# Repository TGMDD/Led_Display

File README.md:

This repository contains schematic and PCB design for a 24X8 Led Display using shift registers 74HC595. 
Note: The PCB is designed for the 5mm flat leds.

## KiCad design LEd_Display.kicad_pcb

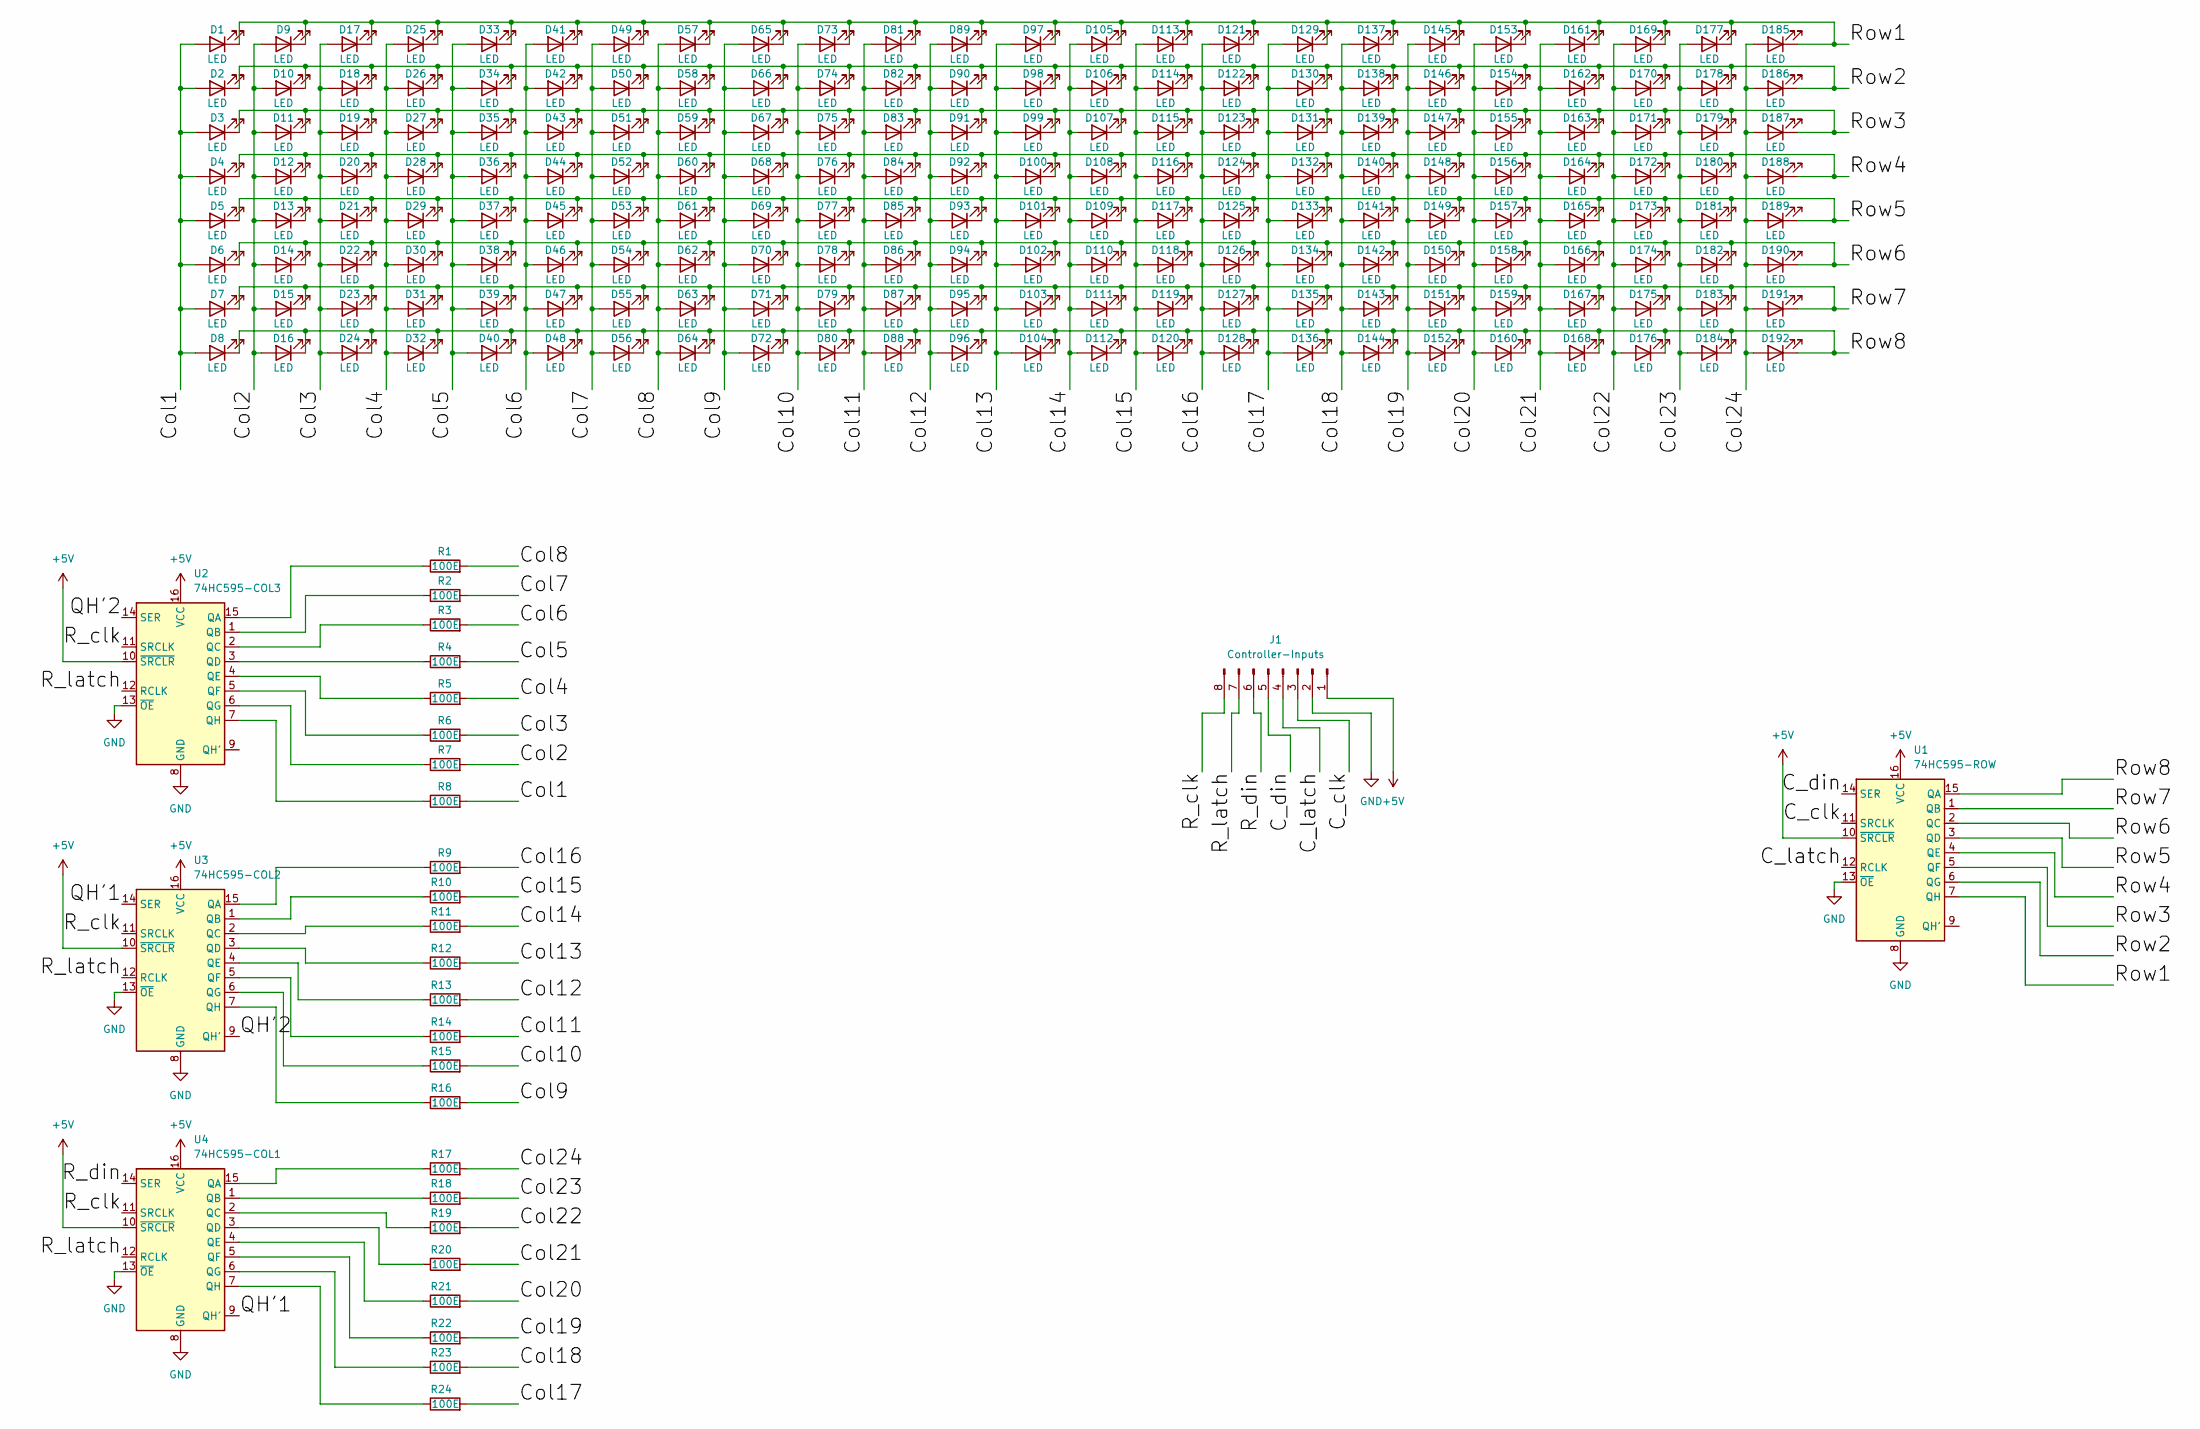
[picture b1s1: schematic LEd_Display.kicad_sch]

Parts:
D1, D2, D3, D4, D5, D6, D7, D8, D9, D10, D11, D12, D13, D14, D15, D16, D17, D18, D19, D20, D21, D22, D23, D24, D25, D26, D27, D28, D29, D30, D31, D32, D33, D34, D35, D36, D37, D38, D39, D40, D41, D42, D43, D44, D45, D46, D47, D48, D49, D50, D51, D52, D53, D54, D55, D56, D57, D58, D59, D60, D61, D62, D63, D64, D65, D66, D67, D68, D69, D70, D71, D72, D73, D74, D75, D76, D77, D78, D79, D80, D81, D82, D83, D84, D85, D86, D87, D88, D89, D90, D91, D92, D93, D94, D95, D96, D97, D98, D99, D100, D101, D102, D103, D104, D105, D106, D107, D108, D109, D110, D111, D112, D113, D114, D115, D116, D117, D118, D119, D120, D121, D122, D123, D124, D125, D126, D127, D128, D129, D130, D131, D132, D133, D134, D135, D136, D137, D138, D139, D140, D141, D142, D143, D144, D145, D146, D147, D148, D149, D150, D151, D152, D153, D154, D155, D156, D157, D158, D159, D160, D161, D162, D163, D164, D165, D166, D167, D168, D169, D170, D171, D172, D173, D174, D175, D176, D177, D178, D179, D180, D181, D182, D183, D184, D185, D186, D187, D188, D189, D190, D191, D192: LED; LED_Rectangular_W5.0mm_H2.0mm
J1: Controller-Inputs; PinHeader_1x08_P2.54mm_Vertical
R1, R2, R3, R4, R5, R6, R7, R8, R9, R10, R11, R12, R13, R14, R15, R16, R17, R18, R19, R20, R21, R22, R23, R24: 100E; R_0805_2012Metric_Pad1.20x1.40mm_HandSolder
U1: 74HC595-ROW; SOP127P600X175-16N
U2: 74HC595-COL3; SOP127P600X175-16N
U3: 74HC595-COL2; SOP127P600X175-16N
U4: 74HC595-COL1; SOP127P600X175-16N

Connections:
+5V: J1.1, U1.10 (~SRCLR), U1.16 (VCC), U2.10 (~SRCLR), U2.16 (VCC), U3.10 (~SRCLR), U3.16 (VCC), U4.10 (~SRCLR), U4.16 (VCC)
/C_clk: J1.3, U1.11 (SRCLK)
/C_din: J1.5, U1.14 (SER)
/C_latch: J1.4, U1.12 (RCLK)
/Col1: D1.2 (A), D2.2 (A), D3.2 (A), D4.2 (A), D5.2 (A), D6.2 (A), D7.2 (A), D8.2 (A), R8.2
/Col2: D9.2 (A), D10.2 (A), D11.2 (A), D12.2 (A), D13.2 (A), D14.2 (A), D15.2 (A), D16.2 (A), R7.2
/Col3: D17.2 (A), D18.2 (A), D19.2 (A), D20.2 (A), D21.2 (A), D22.2 (A), D23.2 (A), D24.2 (A), R6.2
/Col4: D25.2 (A), D26.2 (A), D27.2 (A), D28.2 (A), D29.2 (A), D30.2 (A), D31.2 (A), D32.2 (A), R5.2
/Col5: D33.2 (A), D34.2 (A), D35.2 (A), D36.2 (A), D37.2 (A), D38.2 (A), D39.2 (A), D40.2 (A), R4.2
/Col6: D41.2 (A), D42.2 (A), D43.2 (A), D44.2 (A), D45.2 (A), D46.2 (A), D47.2 (A), D48.2 (A), R3.2
/Col7: D49.2 (A), D50.2 (A), D51.2 (A), D52.2 (A), D53.2 (A), D54.2 (A), D55.2 (A), D56.2 (A), R2.2
/Col8: D57.2 (A), D58.2 (A), D59.2 (A), D60.2 (A), D61.2 (A), D62.2 (A), D63.2 (A), D64.2 (A), R1.2
/Col9: D65.2 (A), D66.2 (A), D67.2 (A), D68.2 (A), D69.2 (A), D70.2 (A), D71.2 (A), D72.2 (A), R16.2
/Col10: D73.2 (A), D74.2 (A), D75.2 (A), D76.2 (A), D77.2 (A), D78.2 (A), D79.2 (A), D80.2 (A), R15.2
/Col11: D81.2 (A), D82.2 (A), D83.2 (A), D84.2 (A), D85.2 (A), D86.2 (A), D87.2 (A), D88.2 (A), R14.2
/Col12: D89.2 (A), D90.2 (A), D91.2 (A), D92.2 (A), D93.2 (A), D94.2 (A), D95.2 (A), D96.2 (A), R13.2
/Col13: D97.2 (A), D98.2 (A), D99.2 (A), D100.2 (A), D101.2 (A), D102.2 (A), D103.2 (A), D104.2 (A), R12.2
/Col14: D105.2 (A), D106.2 (A), D107.2 (A), D108.2 (A), D109.2 (A), D110.2 (A), D111.2 (A), D112.2 (A), R11.2
/Col15: D113.2 (A), D114.2 (A), D115.2 (A), D116.2 (A), D117.2 (A), D118.2 (A), D119.2 (A), D120.2 (A), R10.2
/Col16: D121.2 (A), D122.2 (A), D123.2 (A), D124.2 (A), D125.2 (A), D126.2 (A), D127.2 (A), D128.2 (A), R9.2
/Col17: D129.2 (A), D130.2 (A), D131.2 (A), D132.2 (A), D133.2 (A), D134.2 (A), D135.2 (A), D136.2 (A), R24.2
/Col18: D137.2 (A), D138.2 (A), D139.2 (A), D140.2 (A), D141.2 (A), D142.2 (A), D143.2 (A), D144.2 (A), R23.2
/Col19: D145.2 (A), D146.2 (A), D147.2 (A), D148.2 (A), D149.2 (A), D150.2 (A), D151.2 (A), D152.2 (A), R22.2
/Col20: D153.2 (A), D154.2 (A), D155.2 (A), D156.2 (A), D157.2 (A), D158.2 (A), D159.2 (A), D160.2 (A), R21.2
/Col21: D161.2 (A), D162.2 (A), D163.2 (A), D164.2 (A), D165.2 (A), D166.2 (A), D167.2 (A), D168.2 (A), R20.2
/Col22: D169.2 (A), D170.2 (A), D171.2 (A), D172.2 (A), D173.2 (A), D174.2 (A), D175.2 (A), D176.2 (A), R19.2
/Col23: D177.2 (A), D178.2 (A), D179.2 (A), D180.2 (A), D181.2 (A), D182.2 (A), D183.2 (A), D184.2 (A), R18.2
/Col24: D185.2 (A), D186.2 (A), D187.2 (A), D188.2 (A), D189.2 (A), D190.2 (A), D191.2 (A), D192.2 (A), R17.2
/QH'1: U3.14 (SER), U4.9 (QH')
/QH'2: U2.14 (SER), U3.9 (QH')
/R_clk: J1.8, U2.11 (SRCLK), U3.11 (SRCLK), U4.11 (SRCLK)
/R_din: J1.6, U4.14 (SER)
/R_latch: J1.7, U2.12 (RCLK), U3.12 (RCLK), U4.12 (RCLK)
/Row1: D1.1 (K), D9.1 (K), D17.1 (K), D25.1 (K), D33.1 (K), D41.1 (K), D49.1 (K), D57.1 (K), D65.1 (K), D73.1 (K), D81.1 (K), D89.1 (K), D97.1 (K), D105.1 (K), D113.1 (K), D121.1 (K), D129.1 (K), D137.1 (K), D145.1 (K), D153.1 (K), D161.1 (K), D169.1 (K), D177.1 (K), D185.1 (K), U1.7 (QH)
/Row2: D2.1 (K), D10.1 (K), D18.1 (K), D26.1 (K), D34.1 (K), D42.1 (K), D50.1 (K), D58.1 (K), D66.1 (K), D74.1 (K), D82.1 (K), D90.1 (K), D98.1 (K), D106.1 (K), D114.1 (K), D122.1 (K), D130.1 (K), D138.1 (K), D146.1 (K), D154.1 (K), D162.1 (K), D170.1 (K), D178.1 (K), D186.1 (K), U1.6 (QG)
/Row3: D3.1 (K), D11.1 (K), D19.1 (K), D27.1 (K), D35.1 (K), D43.1 (K), D51.1 (K), D59.1 (K), D67.1 (K), D75.1 (K), D83.1 (K), D91.1 (K), D99.1 (K), D107.1 (K), D115.1 (K), D123.1 (K), D131.1 (K), D139.1 (K), D147.1 (K), D155.1 (K), D163.1 (K), D171.1 (K), D179.1 (K), D187.1 (K), U1.5 (QF)
/Row4: D4.1 (K), D12.1 (K), D20.1 (K), D28.1 (K), D36.1 (K), D44.1 (K), D52.1 (K), D60.1 (K), D68.1 (K), D76.1 (K), D84.1 (K), D92.1 (K), D100.1 (K), D108.1 (K), D116.1 (K), D124.1 (K), D132.1 (K), D140.1 (K), D148.1 (K), D156.1 (K), D164.1 (K), D172.1 (K), D180.1 (K), D188.1 (K), U1.4 (QE)
/Row5: D5.1 (K), D13.1 (K), D21.1 (K), D29.1 (K), D37.1 (K), D45.1 (K), D53.1 (K), D61.1 (K), D69.1 (K), D77.1 (K), D85.1 (K), D93.1 (K), D101.1 (K), D109.1 (K), D117.1 (K), D125.1 (K), D133.1 (K), D141.1 (K), D149.1 (K), D157.1 (K), D165.1 (K), D173.1 (K), D181.1 (K), D189.1 (K), U1.3 (QD)
/Row6: D6.1 (K), D14.1 (K), D22.1 (K), D30.1 (K), D38.1 (K), D46.1 (K), D54.1 (K), D62.1 (K), D70.1 (K), D78.1 (K), D86.1 (K), D94.1 (K), D102.1 (K), D110.1 (K), D118.1 (K), D126.1 (K), D134.1 (K), D142.1 (K), D150.1 (K), D158.1 (K), D166.1 (K), D174.1 (K), D182.1 (K), D190.1 (K), U1.2 (QC)
/Row7: D7.1 (K), D15.1 (K), D23.1 (K), D31.1 (K), D39.1 (K), D47.1 (K), D55.1 (K), D63.1 (K), D71.1 (K), D79.1 (K), D87.1 (K), D95.1 (K), D103.1 (K), D111.1 (K), D119.1 (K), D127.1 (K), D135.1 (K), D143.1 (K), D151.1 (K), D159.1 (K), D167.1 (K), D175.1 (K), D183.1 (K), D191.1 (K), U1.1 (QB)
/Row8: D8.1 (K), D16.1 (K), D24.1 (K), D32.1 (K), D40.1 (K), D48.1 (K), D56.1 (K), D64.1 (K), D72.1 (K), D80.1 (K), D88.1 (K), D96.1 (K), D104.1 (K), D112.1 (K), D120.1 (K), D128.1 (K), D136.1 (K), D144.1 (K), D152.1 (K), D160.1 (K), D168.1 (K), D176.1 (K), D184.1 (K), D192.1 (K), U1.15 (QA)
GND: J1.2, U1.8 (GND), U1.13 (~OE), U2.8 (GND), U2.13 (~OE), U3.8 (GND), U3.13 (~OE), U4.8 (GND), U4.13 (~OE)
unnamed: R1.1, U2.15 (QA)
unnamed: R2.1, U2.1 (QB)
unnamed: R3.1, U2.2 (QC)
unnamed: R4.1, U2.3 (QD)
unnamed: R5.1, U2.4 (QE)
unnamed: R6.1, U2.5 (QF)
unnamed: R7.1, U2.6 (QG)
unnamed: R8.1, U2.7 (QH)
unnamed: R9.1, U3.15 (QA)
unnamed: R10.1, U3.1 (QB)
unnamed: R11.1, U3.2 (QC)
unnamed: R12.1, U3.3 (QD)
unnamed: R13.1, U3.4 (QE)
unnamed: R14.1, U3.5 (QF)
unnamed: R15.1, U3.6 (QG)
unnamed: R16.1, U3.7 (QH)
unnamed: R17.1, U4.15 (QA)
unnamed: R18.1, U4.1 (QB)
unnamed: R19.1, U4.2 (QC)
unnamed: R20.1, U4.3 (QD)
unnamed: R21.1, U4.4 (QE)
unnamed: R22.1, U4.5 (QF)
unnamed: R23.1, U4.6 (QG)
unnamed: R24.1, U4.7 (QH)

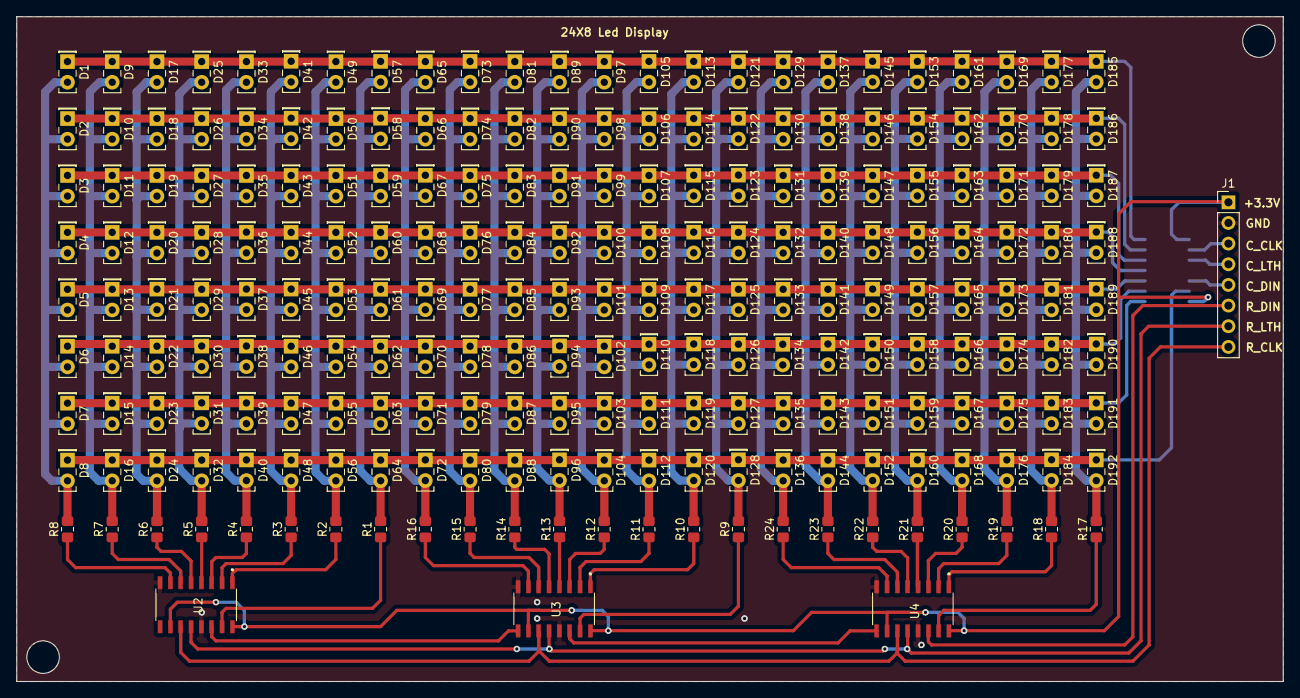
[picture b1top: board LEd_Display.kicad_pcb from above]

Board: 2 copper layers, 155.8 x 81.8 mm, 221 parts (1 on the bottom side), 66 nets.

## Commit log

2024-03-25 Version 1.0
